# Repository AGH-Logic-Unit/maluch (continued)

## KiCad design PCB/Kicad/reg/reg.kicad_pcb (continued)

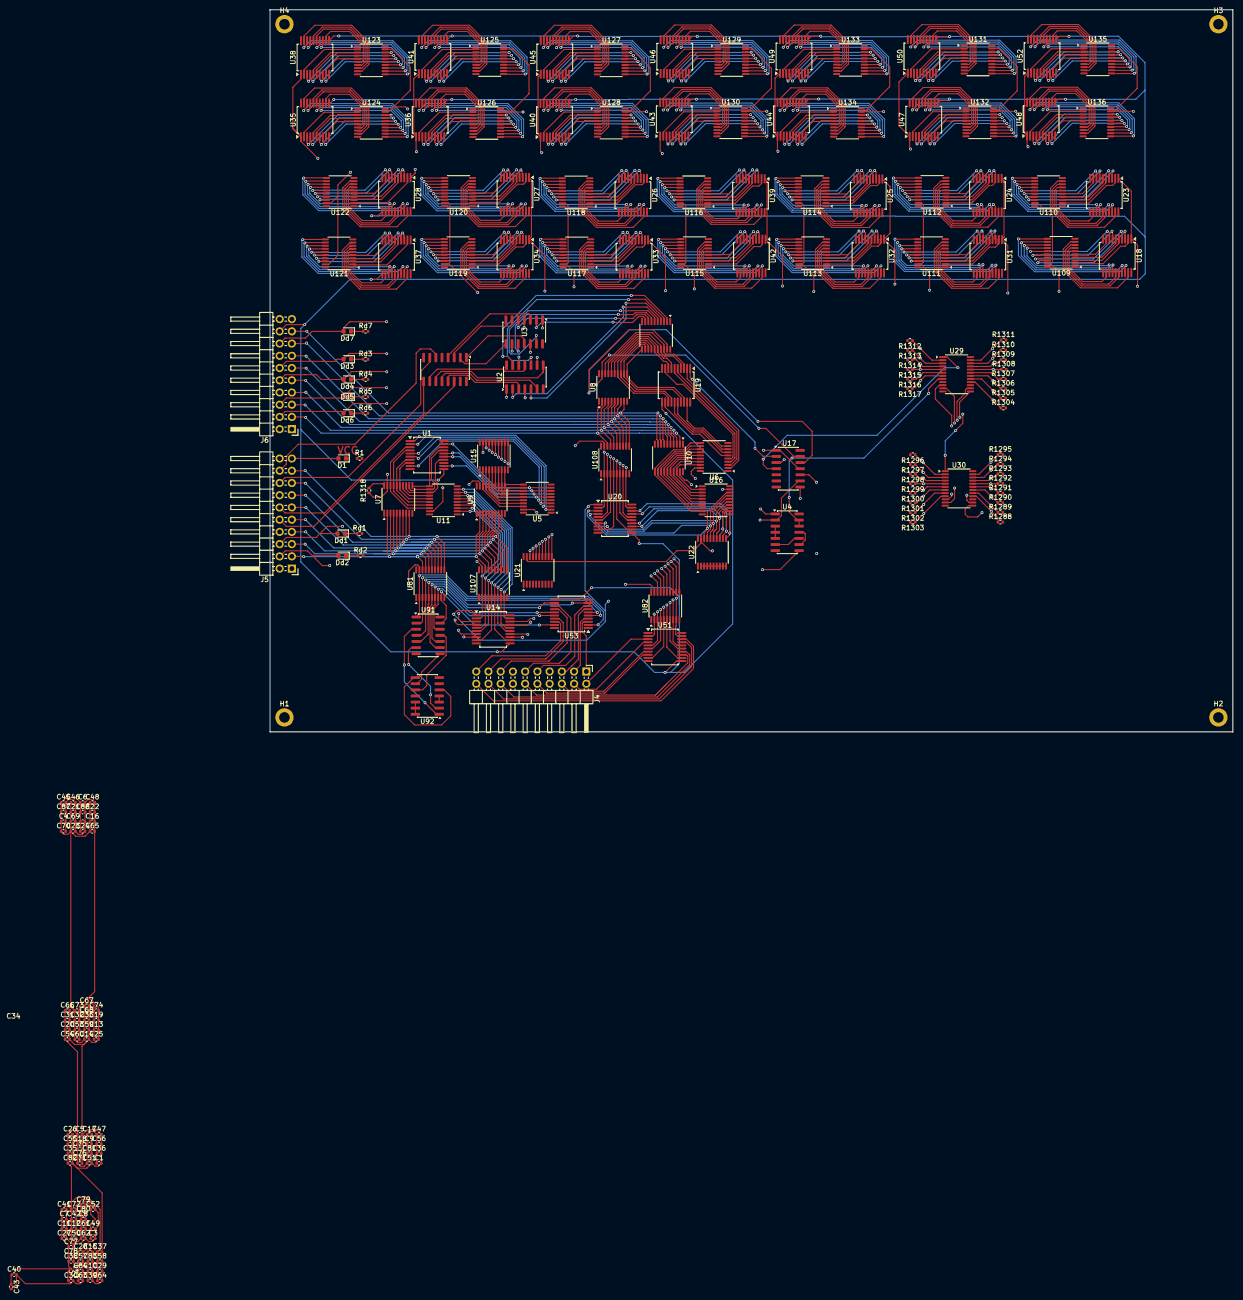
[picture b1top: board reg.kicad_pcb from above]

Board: 6 copper layers, 200.0 x 150.0 mm, 226 parts (0 on the bottom side), 428 nets.

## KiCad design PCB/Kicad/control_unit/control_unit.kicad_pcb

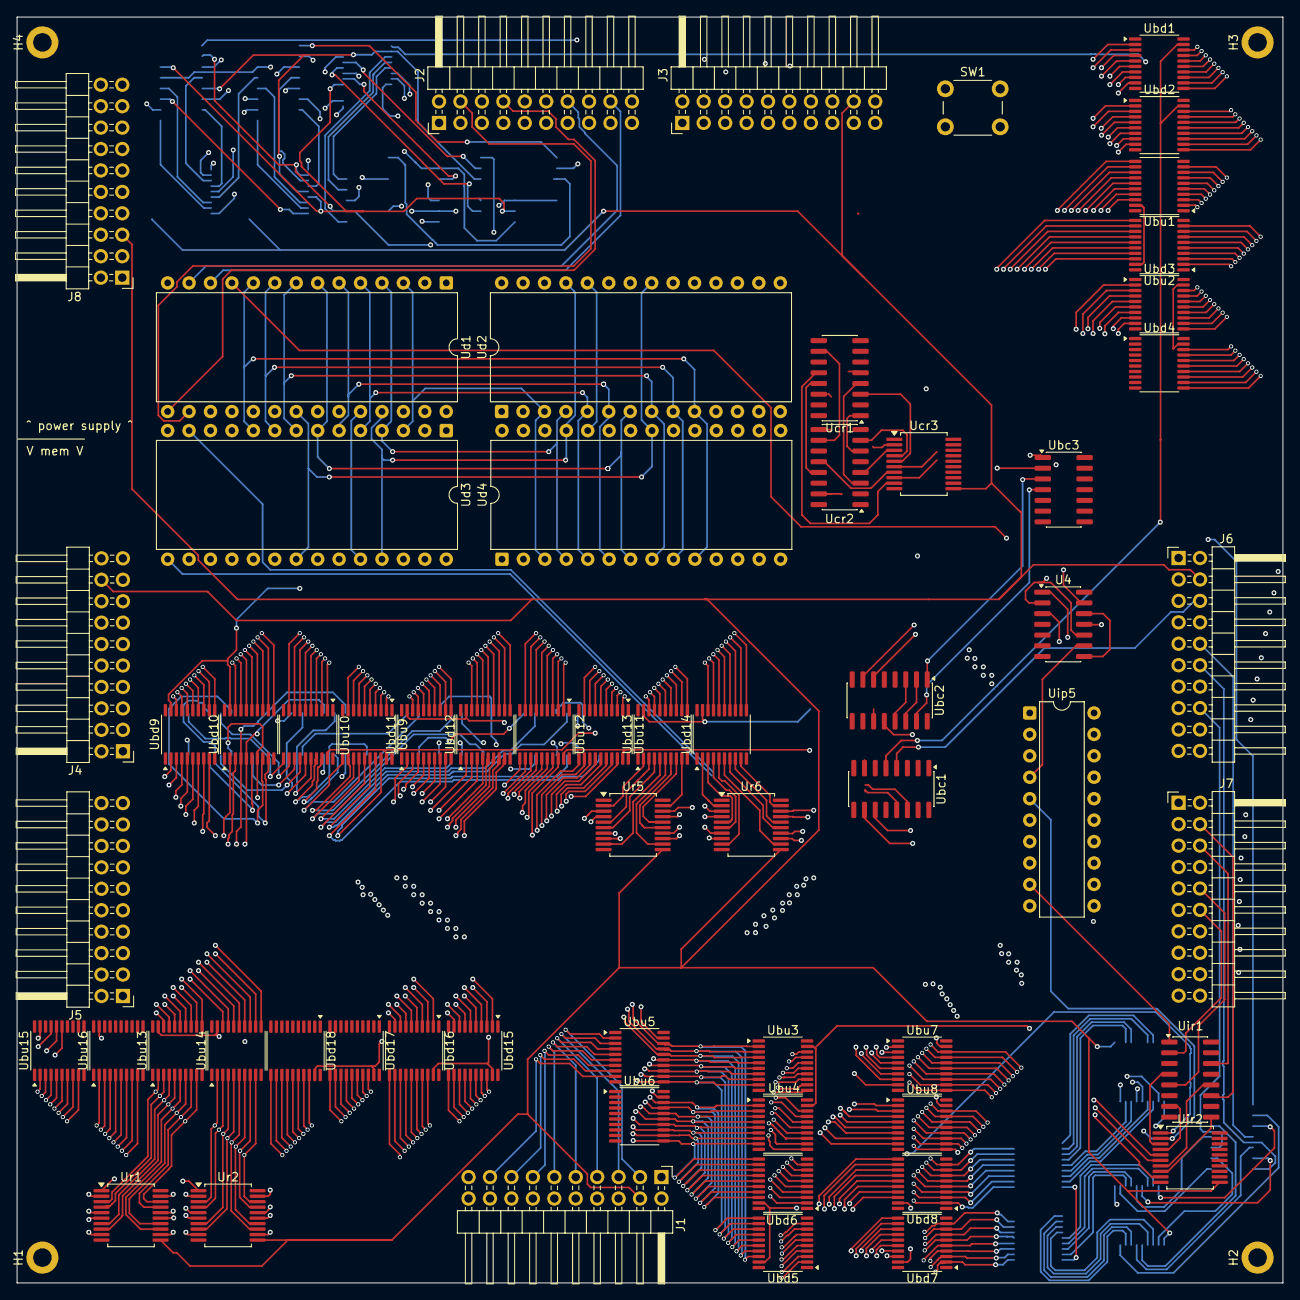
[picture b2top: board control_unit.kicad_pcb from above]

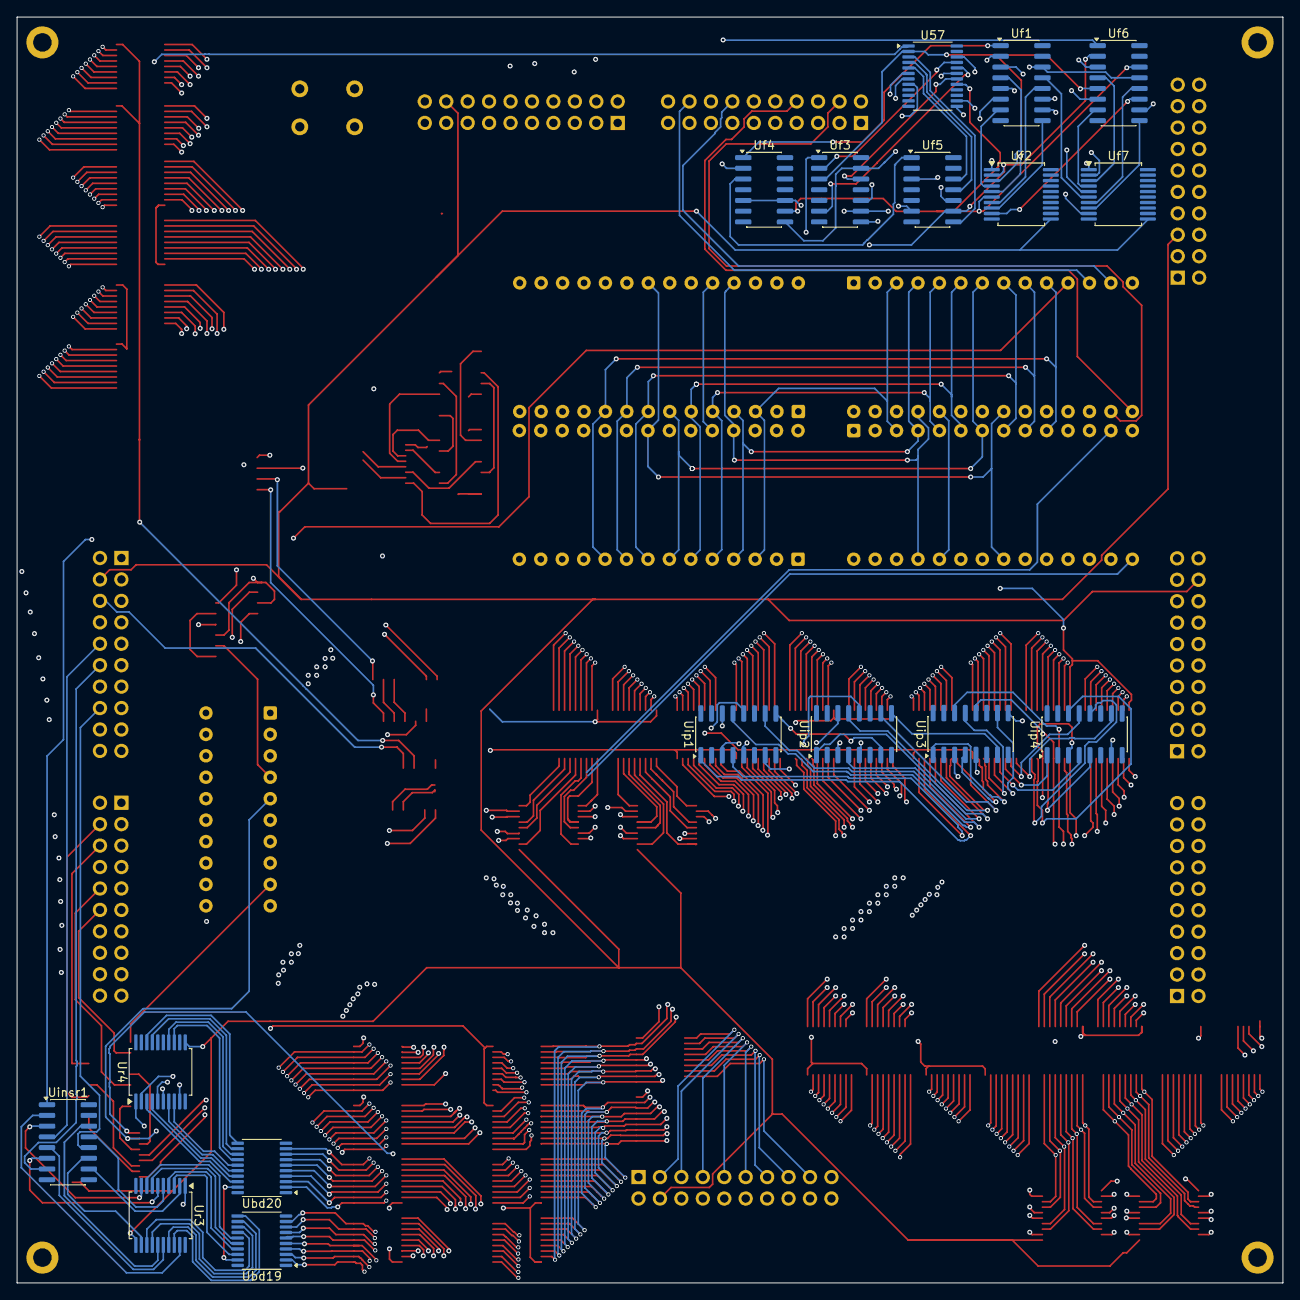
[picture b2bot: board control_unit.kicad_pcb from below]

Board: 6 copper layers, 150.0 x 150.0 mm, 82 parts (17 on the bottom side), 284 nets.

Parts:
H1, H2, H3, H4: MountingHole_Pad; MountingHole_2.2mm_M2_DIN965_Pad
J1, J2, J3, J4, J5, J6, J7, J8: in; PinHeader_2x10_P2.54mm_Horizontal
SW1: SW_Push; SW_PUSH_6mm_H4.3mm
U4: 7408; SO-14_3.9x8.65mm_P1.27mm
U57: 744067; TSSOP-24_4.4x7.8mm_P0.65mm
Ubc1, Ubc2: 74139; SOIC-16_3.9x9.9mm_P1.27mm
Ubc3: 7404; SO-14_3.9x8.65mm_P1.27mm
Ubd1, Ubd2, Ubd3, Ubd4, Ubd5, Ubd6, Ubd7, Ubd8, Ubd9, Ubd10, Ubd11, Ubd12, Ubd13, Ubd14, Ubd15, Ubd16, Ubd17, Ubd18, Ubd19, Ubd20: 74245; TSSOP-20_4.4x6.5mm_P0.65mm
Ubu1, Ubu2, Ubu3, Ubu4, Ubu5, Ubu6, Ubu7, Ubu8, Ubu9, Ubu10, Ubu11, Ubu12, Ubu13, Ubu14, Ubu15, Ubu16: 74245; TSSOP-20_4.4x6.5mm_P0.65mm
Ucr1: 74283; SOIC-16_3.9x9.9mm_P1.27mm
Ucr2: 74257; SOIC-16_3.9x9.9mm_P1.27mm
Ucr3: 74377; SSOP-20_5.3x7.2mm_P0.65mm
Ud1, Ud2, Ud3, Ud4: KM28C64A; DIP-28_W15.24mm
Uf1, Uf6: 74257; SOIC-16_3.9x9.9mm_P1.27mm
Uf2, Uf7: 74377; SSOP-20_5.3x7.2mm_P0.65mm
Uf3: 7404; SO-14_3.9x8.65mm_P1.27mm
Uf4: 7432; SO-14_3.9x8.65mm_P1.27mm
Uf5: 7486; SO-14_3.9x8.65mm_P1.27mm
Uinsr1: 74257; SOIC-16_3.9x9.9mm_P1.27mm
Uip1, Uip2, Uip3, Uip4: 74283; SOIC-16_3.9x9.9mm_P1.27mm
Uip5: ATF16V8Bxx-xxPU; DIP-20_W7.62mm
Uir1: 74257; SOIC-16_3.9x9.9mm_P1.27mm
Uir2: 74377; SSOP-20_5.3x7.2mm_P0.65mm
Ur1, Ur2, Ur3, Ur4, Ur5, Ur6: 74377; SSOP-20_5.3x7.2mm_P0.65mm

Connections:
/ControlUnit/alusrc0: Ubc1.14 (A0), Ud3.13 (I/O2)
/ControlUnit/alusrc1: Ubc1.13 (A1), Ud3.15 (I/O3)
/ControlUnit/buscntrl/srcbus0: Ubd5.18 (B0), Ubu3.2 (A0), Ubu5.18 (B0), Ubu11.18 (B0)
/ControlUnit/buscntrl/srcbus1: Ubd5.17 (B1), Ubu3.3 (A1), Ubu5.17 (B1), Ubu11.17 (B1)
/ControlUnit/buscntrl/srcbus2: Ubd5.16 (B2), Ubu3.4 (A2), Ubu5.16 (B2), Ubu11.16 (B2)
/ControlUnit/buscntrl/srcbus3: Ubd5.15 (B3), Ubu3.5 (A3), Ubu5.15 (B3), Ubu11.15 (B3)
/ControlUnit/buscntrl/srcbus4: Ubd5.14 (B4), Ubu3.6 (A4), Ubu5.14 (B4), Ubu11.14 (B4)
/ControlUnit/buscntrl/srcbus5: Ubd5.13 (B5), Ubu3.7 (A5), Ubu5.13 (B5), Ubu11.13 (B5)
/ControlUnit/buscntrl/srcbus6: Ubd5.12 (B6), Ubu3.8 (A6), Ubu5.12 (B6), Ubu11.12 (B6)
/ControlUnit/buscntrl/srcbus7: Ubd5.11 (B7), Ubu3.9 (A7), Ubu5.11 (B7), Ubu11.11 (B7)
/ControlUnit/buscntrl/srcbus8: Ubd6.18 (B0), Ubu4.2 (A0), Ubu6.18 (B0), Ubu12.18 (B0)
/ControlUnit/buscntrl/srcbus9: Ubd6.17 (B1), Ubu4.3 (A1), Ubu6.17 (B1), Ubu12.17 (B1)
/ControlUnit/buscntrl/srcbus10: Ubd6.16 (B2), Ubu4.4 (A2), Ubu6.16 (B2), Ubu12.16 (B2)
/ControlUnit/buscntrl/srcbus11: Ubd6.15 (B3), Ubu4.5 (A3), Ubu6.15 (B3), Ubu12.15 (B3)
/ControlUnit/buscntrl/srcbus12: Ubd6.14 (B4), Ubu4.6 (A4), Ubu6.14 (B4), Ubu12.14 (B4)
/ControlUnit/buscntrl/srcbus13: Ubd6.13 (B5), Ubu4.7 (A5), Ubu6.13 (B5), Ubu12.13 (B5)
/ControlUnit/buscntrl/srcbus14: Ubd6.12 (B6), Ubu4.8 (A6), Ubu6.12 (B6), Ubu12.12 (B6)
/ControlUnit/buscntrl/srcbus15: Ubd6.11 (B7), Ubu4.9 (A7), Ubu6.11 (B7), Ubu12.11 (B7)
/ControlUnit/buscntrl/~alu_membusen: Ubc1.11 (O1), Ubd7.19 (CE), Ubd8.19 (CE)
/ControlUnit/buscntrl/~alu_regbusen: Ubc1.10 (O2), Ubu7.19 (CE), Ubu8.19 (CE)
/ControlUnit/buscntrl/~mem_ipen: Ubc2.5 (O1), Ubd9.19 (CE), Ubd10.19 (CE)
/ControlUnit/buscntrl/~mem_ipnexten: Ubc2.6 (O2), Ubu9.19 (CE), Ubu10.19 (CE)
/ControlUnit/buscntrl/~mem_regbusen: Ubc2.7 (O3), Ubd11.19 (CE), Ubd12.19 (CE)
/ControlUnit/buscntrl/~mem_srcbusen: Ubc2.12 (O0), Ubu11.19 (CE), Ubu12.19 (CE)
/ControlUnit/buscntrl/~mem_tempregen: Ubc2.11 (O1), Ubd13.19 (CE), Ubd14.19 (CE)
/ControlUnit/buscntrl/~memsrc2: Ubc2.15 (E), Ubc3.4
/ControlUnit/buscntrl/~reg_alubusen: Ubc1.6 (O2), Ubu1.19 (CE), Ubu2.19 (CE)
/ControlUnit/buscntrl/~reg_iobusen: Ubc1.7 (O3), Ubd3.19 (CE), Ubd4.19 (CE)
/ControlUnit/buscntrl/~reg_membusen: Ubc1.5 (O1), Ubd1.19 (CE), Ubd2.19 (CE)
/ControlUnit/buscntrl/~src_regbusen: Ubc3.2, Ubu3.19 (CE), Ubu4.19 (CE)
/ControlUnit/cycle0: Ucr1.5 (A1), Ucr3.2 (Q0), Ud1.7 (A3), Ud2.7 (A3), Ud3.7 (A3), Ud4.7 (A3)
/ControlUnit/cycle1: Ucr1.3 (A2), Ucr3.5 (Q1), Ud1.6 (A4), Ud2.6 (A4), Ud3.6 (A4), Ud4.6 (A4)
/ControlUnit/cycle2: Ucr1.14 (A3), Ucr3.6 (Q2), Ud1.5 (A5), Ud2.5 (A5), Ud3.5 (A5), Ud4.5 (A5)
/ControlUnit/cycle3: Ucr1.12 (A4), Ucr3.9 (Q3), Ud1.4 (A6), Ud2.4 (A6), Ud3.4 (A6), Ud4.4 (A6)
/ControlUnit/flags/c: U57.17 (I14), Uf2.6 (Q2), Uf3.5, Uf4.9, Uf6.14 (I0c)
/ControlUnit/flags/nc: U57.20 (I11), Uf3.6
/ControlUnit/flags/no: U57.16 (I15), Uf3.4
/ControlUnit/flags/ns: U57.21 (I10), Uf3.2
/ControlUnit/flags/nz: U57.7 (I2), Uf3.8
/ControlUnit/flags/o: U57.2 (I7), Uf2.5 (Q1), Uf3.3, Uf5.10, Uf6.5 (I0b)
/ControlUnit/flags/s: U57.22 (I9), Uf2.2 (Q0), Uf3.1, Uf5.9, Uf6.2 (I0a)
/ControlUnit/flags/savedc: Uf1.13 (I1c), Uf7.6 (Q2)
/ControlUnit/flags/savedo: Uf1.6 (I1b), Uf7.5 (Q1)
/ControlUnit/flags/saveds: Uf1.3 (I1a), Uf7.2 (Q0)
/ControlUnit/flags/savedz: Uf1.10 (I1d), Uf7.9 (Q3)
/ControlUnit/flags/z: U57.8 (I1), Uf2.9 (Q3), Uf3.9, Uf4.5, Uf4.10, Uf6.11 (I0d)
/ControlUnit/flwe: Ud2.18 (I/O6), Uf4.2, Uf6.1 (S)
/ControlUnit/instructionregister/buffer_down/out0: Ubd19.18 (B0), Ur3.3 (D0)
/ControlUnit/instructionregister/buffer_down/out1: Ubd19.17 (B1), Ur3.4 (D1)
/ControlUnit/instructionregister/buffer_down/out2: Ubd19.16 (B2), Ur3.7 (D2)
/ControlUnit/instructionregister/buffer_down/out3: Ubd19.15 (B3), Ur3.8 (D3)
/ControlUnit/instructionregister/buffer_down/out4: Ubd19.14 (B4), Ur3.13 (D4)
/ControlUnit/instructionregister/buffer_down/out5: Ubd19.13 (B5), Ur3.14 (D5)
/ControlUnit/instructionregister/buffer_down/out6: Ubd19.12 (B6), Ur3.17 (D6)
/ControlUnit/instructionregister/buffer_down/out7: Ubd19.11 (B7), Ur3.18 (D7)
/ControlUnit/instructionregister/buffer_down/out8: Ubd20.18 (B0), Ur4.3 (D0)
/ControlUnit/instructionregister/buffer_down/out9: Ubd20.17 (B1), Ur4.4 (D1)
/ControlUnit/instructionregister/buffer_down/out10: Ubd20.16 (B2), Ur4.7 (D2)
/ControlUnit/instructionregister/buffer_down/out11: Ubd20.15 (B3), Ur4.8 (D3)
/ControlUnit/instructionregister/buffer_down/out12: Ubd20.14 (B4), Ur4.13 (D4)
/ControlUnit/instructionregister/buffer_down/out13: Ubd20.13 (B5), Ur4.14 (D5)
/ControlUnit/instructionregister/buffer_down/out14: Ubd20.12 (B6), Ur4.17 (D6)
/ControlUnit/instructionregister/buffer_down/out15: Ubd20.11 (B7), Ur4.18 (D7)
/ControlUnit/instructionregister/instr0: Uinsr1.10 (I1d), Ur3.2 (Q0)
/ControlUnit/instructionregister/instr1: Uinsr1.13 (I1c), Ur3.5 (Q1)
/ControlUnit/instructionregister/instr2: Uinsr1.6 (I1b), Ur3.6 (Q2)
/ControlUnit/instructionregister/instr3: Uinsr1.3 (I1a), Ur3.9 (Q3)
/ControlUnit/instructionregister/instr4: Uinsr1.11 (I0d), Ur3.12 (Q4)
/ControlUnit/instructionregister/instr5: Uinsr1.14 (I0c), Ur3.15 (Q5)
/ControlUnit/instructionregister/instr6: Uinsr1.5 (I0b), Ur3.16 (Q6)
/ControlUnit/instructionregister/instr7: Uinsr1.2 (I0a), Ur3.19 (Q7)
/ControlUnit/instructionregister/instr11: Uip1.7 (C0), Ur4.9 (Q3)
/ControlUnit/intidsaved0: Ubu15.17 (B1), Uir2.5 (Q1)
/ControlUnit/intidsaved1: Ubu15.16 (B2), Uir2.6 (Q2)
/ControlUnit/intidsaved2: Ubu15.15 (B3), Uir2.9 (Q3)
/ControlUnit/iosrc: Ubu5.19 (CE), Ubu6.19 (CE), Ud3.16 (I/O4)
/ControlUnit/ip0: Ubd9.2 (A0), Uip1.5 (A1), Ur1.2 (Q0)
/ControlUnit/ip1: Ubd9.3 (A1), Uip1.3 (A2), Ur1.5 (Q1)
/ControlUnit/ip2: Ubd9.4 (A2), Uip1.14 (A3), Ur1.6 (Q2)
/ControlUnit/ip3: Ubd9.5 (A3), Uip1.12 (A4), Ur1.9 (Q3)
/ControlUnit/ip4: Ubd9.6 (A4), Uip2.5 (A1), Ur1.12 (Q4)
/ControlUnit/ip5: Ubd9.7 (A5), Uip2.3 (A2), Ur1.15 (Q5)
/ControlUnit/ip6: Ubd9.8 (A6), Uip2.14 (A3), Ur1.16 (Q6)
/ControlUnit/ip7: Ubd9.9 (A7), Uip2.12 (A4), Ur1.19 (Q7)
/ControlUnit/ip8: Ubd10.2 (A0), Uip3.5 (A1), Ur2.2 (Q0)
/ControlUnit/ip9: Ubd10.3 (A1), Uip3.3 (A2), Ur2.5 (Q1)
/ControlUnit/ip10: Ubd10.4 (A2), Uip3.14 (A3), Ur2.6 (Q2)
/ControlUnit/ip11: Ubd10.5 (A3), Uip3.12 (A4), Ur2.9 (Q3)
/ControlUnit/ip12: Ubd10.6 (A4), Uip4.5 (A1), Ur2.12 (Q4)
/ControlUnit/ip13: Ubd10.7 (A5), Uip4.3 (A2), Ur2.15 (Q5)
/ControlUnit/ip14: Ubd10.8 (A6), Uip4.14 (A3), Ur2.16 (Q6)
/ControlUnit/ip15: Ubd10.9 (A7), Uip4.12 (A4), Ur2.19 (Q7)
/ControlUnit/ip/ipnew0: Ubd15.18 (B0), Ubd17.18 (B0), Ubu13.2 (A0), Ubu15.2 (A0), Ur1.3 (D0)
/ControlUnit/ip/ipnew1: Ubd15.17 (B1), Ubd17.17 (B1), Ubu13.3 (A1), Ubu15.3 (A1), Ur1.4 (D1)
/ControlUnit/ip/ipnew2: Ubd15.16 (B2), Ubd17.16 (B2), Ubu13.4 (A2), Ubu15.4 (A2), Ur1.7 (D2)
/ControlUnit/ip/ipnew3: Ubd15.15 (B3), Ubd17.15 (B3), Ubu13.5 (A3), Ubu15.5 (A3), Ur1.8 (D3)
/ControlUnit/ip/ipnew4: Ubd15.14 (B4), Ubd17.14 (B4), Ubu13.6 (A4), Ubu15.6 (A4), Ur1.13 (D4)
/ControlUnit/ip/ipnew5: Ubd15.13 (B5), Ubd17.13 (B5), Ubu13.7 (A5), Ubu15.7 (A5), Ur1.14 (D5)
/ControlUnit/ip/ipnew6: Ubd15.12 (B6), Ubd17.12 (B6), Ubu13.8 (A6), Ubu15.8 (A6), Ur1.17 (D6)
/ControlUnit/ip/ipnew7: Ubd15.11 (B7), Ubd17.11 (B7), Ubu13.9 (A7), Ubu15.9 (A7), Ur1.18 (D7)
/ControlUnit/ip/ipnew8: Ubd16.18 (B0), Ubd18.18 (B0), Ubu14.2 (A0), Ubu16.2 (A0), Ur2.3 (D0)
/ControlUnit/ip/ipnew9: Ubd16.17 (B1), Ubd18.17 (B1), Ubu14.3 (A1), Ubu16.3 (A1), Ur2.4 (D1)
/ControlUnit/ip/ipnew10: Ubd16.16 (B2), Ubd18.16 (B2), Ubu14.4 (A2), Ubu16.4 (A2), Ur2.7 (D2)
/ControlUnit/ip/ipnew11: Ubd16.15 (B3), Ubd18.15 (B3), Ubu14.5 (A3), Ubu16.5 (A3), Ur2.8 (D3)
/ControlUnit/ip/ipnew12: Ubd16.14 (B4), Ubd18.14 (B4), Ubu14.6 (A4), Ubu16.6 (A4), Ur2.13 (D4)
/ControlUnit/ip/ipnew13: Ubd16.13 (B5), Ubd18.13 (B5), Ubu14.7 (A5), Ubu16.7 (A5), Ur2.14 (D5)
/ControlUnit/ip/ipnew14: Ubd16.12 (B6), Ubd18.12 (B6), Ubu14.8 (A6), Ubu16.8 (A6), Ur2.17 (D6)
/ControlUnit/ip/ipnew15: Ubd16.11 (B7), Ubd18.11 (B7), Ubu14.9 (A7), Ubu16.9 (A7), Ur2.18 (D7)
/ControlUnit/ip/~intidbusen: Ubu15.19 (CE), Ubu16.19 (CE), Uip5.15 (I/O)
/ControlUnit/ip/~ipincen: Ubd15.19 (CE), Ubd16.19 (CE), Uip5.12 (I/O)
/ControlUnit/ip/~membusen: Ubu13.19 (CE), Ubu14.19 (CE), Uip5.14 (I/O)
/ControlUnit/ip/~srcbusen: Ubd17.19 (CE), Ubd18.19 (CE), Uip5.13 (I/O)
/ControlUnit/ipnext0: Ubd15.2 (A0), Ubu9.18 (B0), Uip1.4 (S1)
/ControlUnit/ipnext1: Ubd15.3 (A1), Ubu9.17 (B1), Uip1.1 (S2)
/ControlUnit/ipnext2: Ubd15.4 (A2), Ubu9.16 (B2), Uip1.13 (S3)
/ControlUnit/ipnext3: Ubd15.5 (A3), Ubu9.15 (B3), Uip1.10 (S4)
/ControlUnit/ipnext4: Ubd15.6 (A4), Ubu9.14 (B4), Uip2.4 (S1)
/ControlUnit/ipnext5: Ubd15.7 (A5), Ubu9.13 (B5), Uip2.1 (S2)
/ControlUnit/ipnext6: Ubd15.8 (A6), Ubu9.12 (B6), Uip2.13 (S3)
/ControlUnit/ipnext7: Ubd15.9 (A7), Ubu9.11 (B7), Uip2.10 (S4)
/ControlUnit/ipnext8: Ubd16.2 (A0), Ubu10.18 (B0), Uip3.4 (S1)
/ControlUnit/ipnext9: Ubd16.3 (A1), Ubu10.17 (B1), Uip3.1 (S2)
/ControlUnit/ipnext10: Ubd16.4 (A2), Ubu10.16 (B2), Uip3.13 (S3)
/ControlUnit/ipnext11: Ubd16.5 (A3), Ubu10.15 (B3), Uip3.10 (S4)
/ControlUnit/ipnext12: Ubd16.6 (A4), Ubu10.14 (B4), Uip4.4 (S1)
/ControlUnit/ipnext13: Ubd16.7 (A5), Ubu10.13 (B5), Uip4.1 (S2)
/ControlUnit/ipnext14: Ubd16.8 (A6), Ubu10.12 (B6), Uip4.13 (S3)
/ControlUnit/ipnext15: Ubd16.9 (A7), Ubu10.11 (B7), Uip4.10 (S4)
/ControlUnit/isint: Ubd19.19 (CE), Ubd20.19 (CE), Uip5.5 (I4), Uir2.2 (Q0)
/ControlUnit/isjump: Ud2.16 (I/O4), Uip5.2 (I1)
/ControlUnit/isret: U4.9, Ud1.19 (I/O7), Uip5.4 (I3)
/ControlUnit/isstack: Ud4.11 (I/O0), Uinsr1.15 (OE)
/ControlUnit/memsrc0: Ubc2.2 (A0), Ubc2.14 (A0), Ud3.17 (I/O5)
/ControlUnit/memsrc1: Ubc2.3 (A1), Ubc2.13 (A1), Ud3.18 (I/O6)
/ControlUnit/memsrc2: Ubc2.1 (E), Ubc3.3, Ud3.19 (I/O7)
/ControlUnit/next_instr: U4.2, U4.10, Ubc3.11, Ud1.11 (I/O0)
/ControlUnit/opcode0: U57.13 (S3), Ud1.3 (A7), Ud2.3 (A7), Ud3.3 (A7), Ud4.3 (A7), Ur4.12 (Q4)
/ControlUnit/opcode1: Ud1.25 (A8), Ud2.25 (A8), Ud3.25 (A8), Ud4.25 (A8), Ur4.15 (Q5)
/ControlUnit/opcode2: Ud1.24 (A9), Ud2.24 (A9), Ud3.24 (A9), Ud4.24 (A9), Ur4.16 (Q6)
/ControlUnit/opcode3: Ud1.21 (A10), Ud2.21 (A10), Ud3.21 (A10), Ud4.21 (A10), Ur4.19 (Q7)
/ControlUnit/regds: Ud4.12 (I/O1), Uinsr1.1 (S)
/ControlUnit/regsrc0: Ubc1.2 (A0), Ud3.11 (I/O0)
/ControlUnit/regsrc1: Ubc1.3 (A1), Ud3.12 (I/O1)
/ControlUnit/rst: SW1.2, Ucr2.15 (OE), Uip5.9 (I8), Uir1.1 (S)
/ControlUnit/should_jump: U57.1 (COM_I/O), Uip5.3 (I2)
/ControlUnit/srcsrc: Ubc3.1, Ubd5.19 (CE), Ubd6.19 (CE), Ud2.19 (I/O7)
/ControlUnit/tempreg0: Ubd13.2 (A0), Ur5.2 (Q0)
/ControlUnit/tempreg1: Ubd13.3 (A1), Ur5.5 (Q1)
/ControlUnit/tempreg2: Ubd13.4 (A2), Ur5.6 (Q2)
/ControlUnit/tempreg3: Ubd13.5 (A3), Ur5.9 (Q3)
/ControlUnit/tempreg4: Ubd13.6 (A4), Ur5.12 (Q4)
/ControlUnit/tempreg5: Ubd13.7 (A5), Ur5.15 (Q5)
/ControlUnit/tempreg6: Ubd13.8 (A6), Ur5.16 (Q6)
/ControlUnit/tempreg7: Ubd13.9 (A7), Ur5.19 (Q7)
/ControlUnit/tempreg8: Ubd14.2 (A0), Ur6.2 (Q0)
/ControlUnit/tempreg9: Ubd14.3 (A1), Ur6.5 (Q1)
/ControlUnit/tempreg10: Ubd14.4 (A2), Ur6.6 (Q2)
/ControlUnit/tempreg11: Ubd14.5 (A3), Ur6.9 (Q3)
/ControlUnit/tempreg12: Ubd14.6 (A4), Ur6.12 (Q4)
/ControlUnit/tempreg13: Ubd14.7 (A5), Ur6.15 (Q5)
/ControlUnit/tempreg14: Ubd14.8 (A6), Ur6.16 (Q6)
/ControlUnit/tempreg15: Ubd14.9 (A7), Ur6.19 (Q7)
/ControlUnit/~instr_load: Ud2.11 (I/O0), Ur3.1 (~E), Ur4.1 (~E)
/ControlUnit/~next_instr: Ubc3.10, Ucr2.1 (S), Uir2.1 (~E), Ur1.1 (~E), Ur2.1 (~E)
/ControlUnit/~tempregwe: Ud2.17 (I/O5), Ur5.1 (~E), Ur6.1 (~E)
/alubus0: J3.17, Ubd7.18 (B0), Ubu1.18 (B0), Ubu7.2 (A0)
/alubus1: J3.15, Ubd7.17 (B1), Ubu1.17 (B1), Ubu7.3 (A1)
/alubus2: J3.13, Ubd7.16 (B2), Ubu1.16 (B2), Ubu7.4 (A2)
/alubus3: J3.11, Ubd7.15 (B3), Ubu1.15 (B3), Ubu7.5 (A3)
/alubus4: J3.9, Ubd7.14 (B4), Ubu1.14 (B4), Ubu7.6 (A4)
/alubus5: J3.7, Ubd7.13 (B5), Ubu1.13 (B5), Ubu7.7 (A5)
/alubus6: J3.5, Ubd7.12 (B6), Ubu1.12 (B6), Ubu7.8 (A6)
/alubus7: J3.3, Ubd7.11 (B7), Ubu1.11 (B7), Ubu7.9 (A7)
/alubus8: J2.17, Ubd8.18 (B0), Ubu2.18 (B0), Ubu8.2 (A0)
/alubus9: J2.15, Ubd8.17 (B1), Ubu2.17 (B1), Ubu8.3 (A1)
/alubus10: J2.13, Ubd8.16 (B2), Ubu2.16 (B2), Ubu8.4 (A2)
/alubus11: J2.11, Ubd8.15 (B3), Ubu2.15 (B3), Ubu8.5 (A3)
/alubus12: J2.9, Ubd8.14 (B4), Ubu2.14 (B4), Ubu8.6 (A4)
/alubus13: J2.7, Ubd8.13 (B5), Ubu2.13 (B5), Ubu8.7 (A5)
/alubus14: J2.5, Ubd8.12 (B6), Ubu2.12 (B6), Ubu8.8 (A6)
/alubus15: J2.3, Ubd8.11 (B7), Ubu2.11 (B7), Ubu8.9 (A7)
/aluop0: J2.18, Ud1.12 (I/O1)
/aluop1: J2.14, Ud1.13 (I/O2)
/aluop2: J2.8, Ud1.15 (I/O3)
/aluop3: J2.4, Ud1.16 (I/O4)
/clk: J1.4, J3.18, J4.18, J6.4, J8.3, J8.5, Ucr3.11 (CP), Uf2.11 (CP), Uf7.11 (CP), Uir2.11 (CP), Ur1.11 (CP), Ur2.11 (CP), Ur3.11 (CP), Ur4.11 (CP), Ur5.11 (CP), Ur6.11 (CP)
/fc: J3.10, Uf1.14 (I0c), Uf6.13 (I1c)
/fo: J3.6, Uf1.5 (I0b), Uf6.6 (I1b)
/fs: J3.4, Uf1.2 (I0a), Uf6.3 (I1a)
/fz: J3.12, Uf1.11 (I0d), Uf6.10 (I1d)
/int: J7.12, U4.1, Uir1.2 (I0a)
/intid0: J7.10, Uir1.5 (I0b)
/intid1: J7.6, Uir1.14 (I0c)
/intid2: J7.4, Uir1.11 (I0d)
/iobus0: J1.3, Ubd3.2 (A0), Ubu5.2 (A0)
/iobus1: J1.5, Ubd3.3 (A1), Ubu5.3 (A1)
/iobus2: J1.7, Ubd3.4 (A2), Ubu5.4 (A2)
/iobus3: J1.9, Ubd3.5 (A3), Ubu5.5 (A3)
/iobus4: J1.11, Ubd3.6 (A4), Ubu5.6 (A4)
/iobus5: J1.13, Ubd3.7 (A5), Ubu5.7 (A5)
/iobus6: J1.15, Ubd3.8 (A6), Ubu5.8 (A6)
/iobus7: J1.17, Ubd3.9 (A7), Ubu5.9 (A7)
/iocmd0: J1.16, Ud1.17 (I/O5)
/iocmd1: J1.18, Ud1.18 (I/O6)
/ioid0: J1.6, U4.13, U57.10 (S0), Ud1.10 (A0), Ud2.10 (A0), Ud3.10 (A0), Ud4.10 (A0), Ur4.2 (Q0)
/ioid1: J1.10, U57.11 (S1), Ud1.9 (A1), Ud2.9 (A1), Ud3.9 (A1), Ud4.9 (A1), Ur4.5 (Q1)
/ioid2: J1.12, U57.14 (S2), Ud1.8 (A2), Ud2.8 (A2), Ud3.8 (A2), Ud4.8 (A2), Ur4.6 (Q2)
/mask_restore: J7.18, U4.11, Uf1.1 (S), Uf4.1
/mask_save: J7.16, U4.3, Uf5.4
/membus0: J5.3, Ubd1.2 (A0), Ubd5.2 (A0), Ubd7.2 (A0), Ubd9.18 (B0), Ubd11.18 (B0), Ubd13.18 (B0), Ubd19.2 (A0), Ubu9.2 (A0), Ubu11.2 (A0), Ubu13.18 (B0), Ur5.3 (D0)
/membus1: J5.5, Ubd1.3 (A1), Ubd5.3 (A1), Ubd7.3 (A1), Ubd9.17 (B1), Ubd11.17 (B1), Ubd13.17 (B1), Ubd19.3 (A1), Ubu9.3 (A1), Ubu11.3 (A1), Ubu13.17 (B1), Ur5.4 (D1)
/membus2: J5.7, Ubd1.4 (A2), Ubd5.4 (A2), Ubd7.4 (A2), Ubd9.16 (B2), Ubd11.16 (B2), Ubd13.16 (B2), Ubd19.4 (A2), Ubu9.4 (A2), Ubu11.4 (A2), Ubu13.16 (B2), Ur5.7 (D2)
/membus3: J5.9, Ubd1.5 (A3), Ubd5.5 (A3), Ubd7.5 (A3), Ubd9.15 (B3), Ubd11.15 (B3), Ubd13.15 (B3), Ubd19.5 (A3), Ubu9.5 (A3), Ubu11.5 (A3), Ubu13.15 (B3), Ur5.8 (D3)
/membus4: J5.11, Ubd1.6 (A4), Ubd5.6 (A4), Ubd7.6 (A4), Ubd9.14 (B4), Ubd11.14 (B4), Ubd13.14 (B4), Ubd19.6 (A4), Ubu9.6 (A4), Ubu11.6 (A4), Ubu13.14 (B4), Ur5.13 (D4)
/membus5: J5.13, Ubd1.7 (A5), Ubd5.7 (A5), Ubd7.7 (A5), Ubd9.13 (B5), Ubd11.13 (B5), Ubd13.13 (B5), Ubd19.7 (A5), Ubu9.7 (A5), Ubu11.7 (A5), Ubu13.13 (B5), Ur5.14 (D5)
/membus6: J5.15, Ubd1.8 (A6), Ubd5.8 (A6), Ubd7.8 (A6), Ubd9.12 (B6), Ubd11.12 (B6), Ubd13.12 (B6), Ubd19.8 (A6), Ubu9.8 (A6), Ubu11.8 (A6), Ubu13.12 (B6), Ur5.17 (D6)
/membus7: J5.17, Ubd1.9 (A7), Ubd5.9 (A7), Ubd7.9 (A7), Ubd9.11 (B7), Ubd11.11 (B7), Ubd13.11 (B7), Ubd19.9 (A7), Ubu9.9 (A7), Ubu11.9 (A7), Ubu13.11 (B7), Ur5.18 (D7)
/membus8: J4.3, Ubd2.2 (A0), Ubd6.2 (A0), Ubd8.2 (A0), Ubd10.18 (B0), Ubd12.18 (B0), Ubd14.18 (B0), Ubd20.2 (A0), Ubu10.2 (A0), Ubu12.2 (A0), Ubu14.18 (B0), Ur6.3 (D0)
/membus9: J4.5, Ubd2.3 (A1), Ubd6.3 (A1), Ubd8.3 (A1), Ubd10.17 (B1), Ubd12.17 (B1), Ubd14.17 (B1), Ubd20.3 (A1), Ubu10.3 (A1), Ubu12.3 (A1), Ubu14.17 (B1), Ur6.4 (D1)
/membus10: J4.7, Ubd2.4 (A2), Ubd6.4 (A2), Ubd8.4 (A2), Ubd10.16 (B2), Ubd12.16 (B2), Ubd14.16 (B2), Ubd20.4 (A2), Ubu10.4 (A2), Ubu12.4 (A2), Ubu14.16 (B2), Ur6.7 (D2)
/membus11: J4.9, Ubd2.5 (A3), Ubd6.5 (A3), Ubd8.5 (A3), Ubd10.15 (B3), Ubd12.15 (B3), Ubd14.15 (B3), Ubd20.5 (A3), Ubu10.5 (A3), Ubu12.5 (A3), Ubu14.15 (B3), Ur6.8 (D3)
/membus12: J4.11, Ubd2.6 (A4), Ubd6.6 (A4), Ubd8.6 (A4), Ubd10.14 (B4), Ubd12.14 (B4), Ubd14.14 (B4), Ubd20.6 (A4), Ubu10.6 (A4), Ubu12.6 (A4), Ubu14.14 (B4), Ur6.13 (D4)
/membus13: J4.13, Ubd2.7 (A5), Ubd6.7 (A5), Ubd8.7 (A5), Ubd10.13 (B5), Ubd12.13 (B5), Ubd14.13 (B5), Ubd20.7 (A5), Ubu10.7 (A5), Ubu12.7 (A5), Ubu14.13 (B5), Ur6.14 (D5)
/membus14: J4.15, Ubd2.8 (A6), Ubd6.8 (A6), Ubd8.8 (A6), Ubd10.12 (B6), Ubd12.12 (B6), Ubd14.12 (B6), Ubd20.8 (A6), Ubu10.8 (A6), Ubu12.8 (A6), Ubu14.12 (B6), Ur6.17 (D6)
/membus15: J4.17, Ubd2.9 (A7), Ubd6.9 (A7), Ubd8.9 (A7), Ubd10.11 (B7), Ubd12.11 (B7), Ubd14.11 (B7), Ubd20.9 (A7), Ubu10.9 (A7), Ubu12.9 (A7), Ubu14.11 (B7), Ur6.18 (D7)
/memop0: J5.4, Ud2.12 (I/O1)
/memop1: J5.8, Ud2.13 (I/O2)
/memop2: J5.12, Ud2.15 (I/O3)
/regbus0: J7.17, Ubd1.18 (B0), Ubd3.18 (B0), Ubd11.2 (A0), Ubu1.2 (A0), Ubu3.18 (B0), Ubu7.18 (B0)
/regbus1: J7.15, Ubd1.17 (B1), Ubd3.17 (B1), Ubd11.3 (A1), Ubu1.3 (A1), Ubu3.17 (B1), Ubu7.17 (B1)
/regbus2: J7.13, Ubd1.16 (B2), Ubd3.16 (B2), Ubd11.4 (A2), Ubu1.4 (A2), Ubu3.16 (B2), Ubu7.16 (B2)
/regbus3: J7.11, Ubd1.15 (B3), Ubd3.15 (B3), Ubd11.5 (A3), Ubu1.5 (A3), Ubu3.15 (B3), Ubu7.15 (B3)
/regbus4: J7.9, Ubd1.14 (B4), Ubd3.14 (B4), Ubd11.6 (A4), Ubu1.6 (A4), Ubu3.14 (B4), Ubu7.14 (B4)
/regbus5: J7.7, Ubd1.13 (B5), Ubd3.13 (B5), Ubd11.7 (A5), Ubu1.7 (A5), Ubu3.13 (B5), Ubu7.13 (B5)
/regbus6: J7.5, Ubd1.12 (B6), Ubd3.12 (B6), Ubd11.8 (A6), Ubu1.8 (A6), Ubu3.12 (B6), Ubu7.12 (B6)
/regbus7: J7.3, Ubd1.11 (B7), Ubd3.11 (B7), Ubd11.9 (A7), Ubu1.9 (A7), Ubu3.11 (B7), Ubu7.11 (B7)
/regbus8: J6.17, Ubd2.18 (B0), Ubd4.18 (B0), Ubd12.2 (A0), Ubu2.2 (A0), Ubu4.18 (B0), Ubu8.18 (B0)
/regbus9: J6.15, Ubd2.17 (B1), Ubd4.17 (B1), Ubd12.3 (A1), Ubu2.3 (A1), Ubu4.17 (B1), Ubu8.17 (B1)
/regbus10: J6.13, Ubd2.16 (B2), Ubd4.16 (B2), Ubd12.4 (A2), Ubu2.4 (A2), Ubu4.16 (B2), Ubu8.16 (B2)
/regbus11: J6.11, Ubd2.15 (B3), Ubd4.15 (B3), Ubd12.5 (A3), Ubu2.5 (A3), Ubu4.15 (B3), Ubu8.15 (B3)
/regbus12: J6.9, Ubd2.14 (B4), Ubd4.14 (B4), Ubd12.6 (A4), Ubu2.6 (A4), Ubu4.14 (B4), Ubu8.14 (B4)
/regbus13: J6.7, Ubd2.13 (B5), Ubd4.13 (B5), Ubd12.7 (A5), Ubu2.7 (A5), Ubu4.13 (B5), Ubu8.13 (B5)
/regbus14: J6.5, Ubd2.12 (B6), Ubd4.12 (B6), Ubd12.8 (A6), Ubu2.8 (A6), Ubu4.12 (B6), Ubu8.12 (B6)
/regbus15: J6.3, Ubd2.11 (B7), Ubd4.11 (B7), Ubd12.9 (A7), Ubu2.9 (A7), Ubu4.11 (B7), Ubu8.11 (B7)
/regwe: J6.6, Ubc1.4 (O0)
/rid0: J6.18, Uinsr1.9 (Zd)
/rid1: J6.16, Uinsr1.12 (Zc)
/rid2: J6.12, Uinsr1.7 (Zb)
/rid3: J6.10, Uinsr1.4 (Za)
GND: H1.1 (1_1), H2.1 (1_1), H3.1 (1_1), H4.1 (1_1), J1.2, J1.8, J1.14, J1.20, J2.2, J2.6, J2.10, J2.12, J2.16, J2.20, J3.2, J3.8, J3.14, J3.16, J3.20, J4.2, J4.4, J4.6, J4.8, J4.10, J4.12, J4.14, J4.16, J4.20, J5.2, J5.6, J5.10, J5.14, J5.16, J5.18, J5.20, J6.2, J6.8, J6.14, J6.20, J7.2, J7.8, J7.14, J7.20, J8.1, J8.2, J8.4, J8.6, J8.7, J8.8, J8.10, J8.12, J8.14, J8.16, J8.18, J8.20, U4.7 (GND), U57.12 (GND), U57.15 (~E), U57.23 (I8), Ubc1.1 (E), Ubc1.8 (GND), Ubc1.15 (E), Ubc2.8 (GND), Ubc3.7 (GND), Ubd1.10 (GND), Ubd2.10 (GND), Ubd3.10 (GND), Ubd4.2 (A0), Ubd4.3 (A1), Ubd4.4 (A2), Ubd4.5 (A3), Ubd4.6 (A4), Ubd4.7 (A5), Ubd4.8 (A6), Ubd4.9 (A7), Ubd4.10 (GND), Ubd5.10 (GND), Ubd6.10 (GND), Ubd7.10 (GND), Ubd8.10 (GND), Ubd9.10 (GND), Ubd10.10 (GND), Ubd11.10 (GND), Ubd12.10 (GND), Ubd13.10 (GND), Ubd14.10 (GND), Ubd15.10 (GND), Ubd16.10 (GND), Ubd17.10 (GND), Ubd18.10 (GND), Ubd19.10 (GND), Ubd20.10 (GND), Ubu1.1 (A->B), Ubu1.10 (GND), Ubu2.1 (A->B), Ubu2.10 (GND), Ubu3.1 (A->B), Ubu3.10 (GND), Ubu4.1 (A->B), Ubu4.10 (GND), Ubu5.1 (A->B), Ubu5.10 (GND), Ubu6.1 (A->B), Ubu6.2 (A0), Ubu6.3 (A1), Ubu6.4 (A2), Ubu6.5 (A3), Ubu6.6 (A4), Ubu6.7 (A5), Ubu6.8 (A6), Ubu6.9 (A7), Ubu6.10 (GND), Ubu7.1 (A->B), Ubu7.10 (GND), Ubu8.1 (A->B), Ubu8.10 (GND), Ubu9.1 (A->B), Ubu9.10 (GND), Ubu10.1 (A->B), Ubu10.10 (GND), Ubu11.1 (A->B), Ubu11.10 (GND), Ubu12.1 (A->B), Ubu12.10 (GND), Ubu13.1 (A->B), Ubu13.10 (GND), Ubu14.1 (A->B), Ubu14.10 (GND), Ubu15.1 (A->B), Ubu15.10 (GND), Ubu15.18 (B0), Ubu16.1 (A->B), Ubu16.10 (GND), Ucr1.2 (B2), Ucr1.6 (B1), Ucr1.8 (GND), Ucr1.11 (B4), Ucr1.15 (B3), Ucr2.2 (I0a), Ucr2.5 (I0b), Ucr2.8 (GND), Ucr2.11 (I0d), Ucr2.14 (I0c), Ucr3.1 (~E), Ucr3.10 (GND), Ud1.2 (A12), Ud1.14 (GND), Ud1.20 (~CE), Ud1.22 (~OE), Ud1.23 (A11), Ud2.2 (A12), Ud2.14 (GND), Ud2.20 (~CE), Ud2.22 (~OE), Ud2.23 (A11), Ud3.2 (A12), Ud3.14 (GND), Ud3.20 (~CE), Ud3.22 (~OE), Ud3.23 (A11), Ud4.2 (A12), Ud4.14 (GND), Ud4.20 (~CE), Ud4.22 (~OE), Ud4.23 (A11), Uf1.8 (GND), Uf1.15 (OE), Uf2.10 (GND), Uf3.7 (GND), Uf4.7 (GND), Uf5.7 (GND), Uf6.8 (GND), Uf6.15 (OE), Uf7.10 (GND), Uinsr1.8 (GND), Uip1.2 (B2), Uip1.8 (GND), Uip1.11 (B4), Uip1.15 (B3), Uip2.2 (B2), Uip2.6 (B1), Uip2.8 (GND), Uip2.11 (B4), Uip2.15 (B3), Uip3.2 (B2), Uip3.6 (B1), Uip3.8 (GND), Uip3.11 (B4), Uip3.15 (B3), Uip4.2 (B2), Uip4.6 (B1), Uip4.8 (GND), Uip4.11 (B4), Uip4.15 (B3), Uip5.1 (I), Uip5.6 (I5), Uip5.7 (I6), Uip5.8 (I7), Uip5.10 (GND), Uip5.11 (I9), Uir1.3 (I1a), Uir1.6 (I1b), Uir1.8 (GND), Uir1.10 (I1d), Uir1.13 (I1c), Uir1.15 (OE), Uir2.10 (GND), Ur1.10 (GND), Ur2.10 (GND), Ur3.10 (GND), Ur4.10 (GND), Ur5.10 (GND), Ur6.10 (GND)
unnamed: U4.8, U4.12
unnamed: U57.6 (I3), Uf3.10
unnamed: U57.5 (I4), Uf4.6, Uf5.12
unnamed: U57.4 (I5), Uf5.11
unnamed: U57.3 (I6), Uf3.11, Uf4.4, Uf5.8
unnamed: U57.19 (I12), Uf3.13, Uf4.8
unnamed: U57.18 (I13), Uf3.12
unnamed: Ucr1.4 (S1), Ucr2.3 (I1a)
unnamed: Ucr1.1 (S2), Ucr2.6 (I1b)
unnamed: Ucr1.13 (S3), Ucr2.13 (I1c)
unnamed: Ucr1.10 (S4), Ucr2.10 (I1d)
unnamed: Ucr2.4 (Za), Ucr3.3 (D0)
unnamed: Ucr2.7 (Zb), Ucr3.4 (D1)
unnamed: Ucr2.12 (Zc), Ucr3.7 (D2)
unnamed: Ucr2.9 (Zd), Ucr3.8 (D3)
unnamed: Uf1.4 (Za), Uf2.3 (D0)
unnamed: Uf1.7 (Zb), Uf2.4 (D1)
unnamed: Uf1.12 (Zc), Uf2.7 (D2)
unnamed: Uf1.9 (Zd), Uf2.8 (D3)
unnamed: Uf2.1 (~E), Uf5.3
unnamed: Uf4.3, Uf5.1
unnamed: Uf6.4 (Za), Uf7.3 (D0)
unnamed: Uf6.7 (Zb), Uf7.4 (D1)
unnamed: Uf6.12 (Zc), Uf7.7 (D2)
unnamed: Uf6.9 (Zd), Uf7.8 (D3)
unnamed: Uf5.6, Uf7.1 (~E)
unnamed: Uip1.9 (C4), Uip2.7 (C0)
unnamed: Uip2.9 (C4), Uip3.7 (C0)
unnamed: Uip3.9 (C4), Uip4.7 (C0)
unnamed: Uir1.4 (Za), Uir2.3 (D0)
unnamed: Uir1.7 (Zb), Uir2.4 (D1)
unnamed: Uir1.12 (Zc), Uir2.7 (D2)
unnamed: Uir1.9 (Zd), Uir2.8 (D3)
VCC: J1.1, J1.19, J2.1, J2.19, J3.1, J3.19, J4.1, J4.19, J5.1, J5.19, J6.1, J6.19, J7.1, J7.19, J8.9, J8.11, J8.13, J8.15, J8.17, J8.19, SW1.1, U4.4, U4.5, U4.14 (VCC), U57.9 (I0), U57.24 (VCC), Ubc1.16 (VCC), Ubc2.16 (VCC), Ubc3.5, Ubc3.9, Ubc3.13, Ubc3.14 (VCC), Ubd1.1 (A->B), Ubd1.20 (VCC), Ubd2.1 (A->B), Ubd2.20 (VCC), Ubd3.1 (A->B), Ubd3.20 (VCC), Ubd4.1 (A->B), Ubd4.20 (VCC), Ubd5.1 (A->B), Ubd5.20 (VCC), Ubd6.1 (A->B), Ubd6.20 (VCC), Ubd7.1 (A->B), Ubd7.20 (VCC), Ubd8.1 (A->B), Ubd8.20 (VCC), Ubd9.1 (A->B), Ubd9.20 (VCC), Ubd10.1 (A->B), Ubd10.20 (VCC), Ubd11.1 (A->B), Ubd11.20 (VCC), Ubd12.1 (A->B), Ubd12.20 (VCC), Ubd13.1 (A->B), Ubd13.20 (VCC), Ubd14.1 (A->B), Ubd14.20 (VCC), Ubd15.1 (A->B), Ubd15.20 (VCC), Ubd16.1 (A->B), Ubd16.20 (VCC), Ubd17.1 (A->B), Ubd17.20 (VCC), Ubd18.1 (A->B), Ubd18.20 (VCC), Ubd19.1 (A->B), Ubd19.20 (VCC), Ubd20.1 (A->B), Ubd20.20 (VCC), Ubu1.20 (VCC), Ubu2.20 (VCC), Ubu3.20 (VCC), Ubu4.20 (VCC), Ubu5.20 (VCC), Ubu6.20 (VCC), Ubu7.20 (VCC), Ubu8.20 (VCC), Ubu9.20 (VCC), Ubu10.20 (VCC), Ubu11.20 (VCC), Ubu12.20 (VCC), Ubu13.20 (VCC), Ubu14.20 (VCC), Ubu15.11 (B7), Ubu15.12 (B6), Ubu15.13 (B5), Ubu15.14 (B4), Ubu15.20 (VCC), Ubu16.11 (B7), Ubu16.12 (B6), Ubu16.13 (B5), Ubu16.14 (B4), Ubu16.15 (B3), Ubu16.16 (B2), Ubu16.17 (B1), Ubu16.18 (B0), Ubu16.20 (VCC), Ucr1.7 (C0), Ucr1.16 (VCC), Ucr2.16 (VCC), Ucr3.13 (D4), Ucr3.14 (D5), Ucr3.17 (D6), Ucr3.18 (D7), Ucr3.20 (VCC), Ud1.27 (~WE), Ud1.28 (VCC), Ud2.27 (~WE), Ud2.28 (VCC), Ud3.27 (~WE), Ud3.28 (VCC), Ud4.27 (~WE), Ud4.28 (VCC), Uf1.16 (VCC), Uf2.13 (D4), Uf2.14 (D5), Uf2.17 (D6), Uf2.18 (D7), Uf2.20 (VCC), Uf3.14 (VCC), Uf4.12, Uf4.13, Uf4.14 (VCC), Uf5.2, Uf5.5, Uf5.13, Uf5.14 (VCC), Uf6.16 (VCC), Uf7.13 (D4), Uf7.14 (D5), Uf7.17 (D6), Uf7.18 (D7), Uf7.20 (VCC), Uinsr1.16 (VCC), Uip1.6 (B1), Uip1.16 (VCC), Uip2.16 (VCC), Uip3.16 (VCC), Uip4.16 (VCC), Uip5.20 (V_{CC}), Uir1.16 (VCC), Uir2.13 (D4), Uir2.14 (D5), Uir2.17 (D6), Uir2.18 (D7), Uir2.20 (VCC), Ur1.20 (VCC), Ur2.20 (VCC), Ur3.20 (VCC), Ur4.20 (VCC), Ur5.20 (VCC), Ur6.20 (VCC)

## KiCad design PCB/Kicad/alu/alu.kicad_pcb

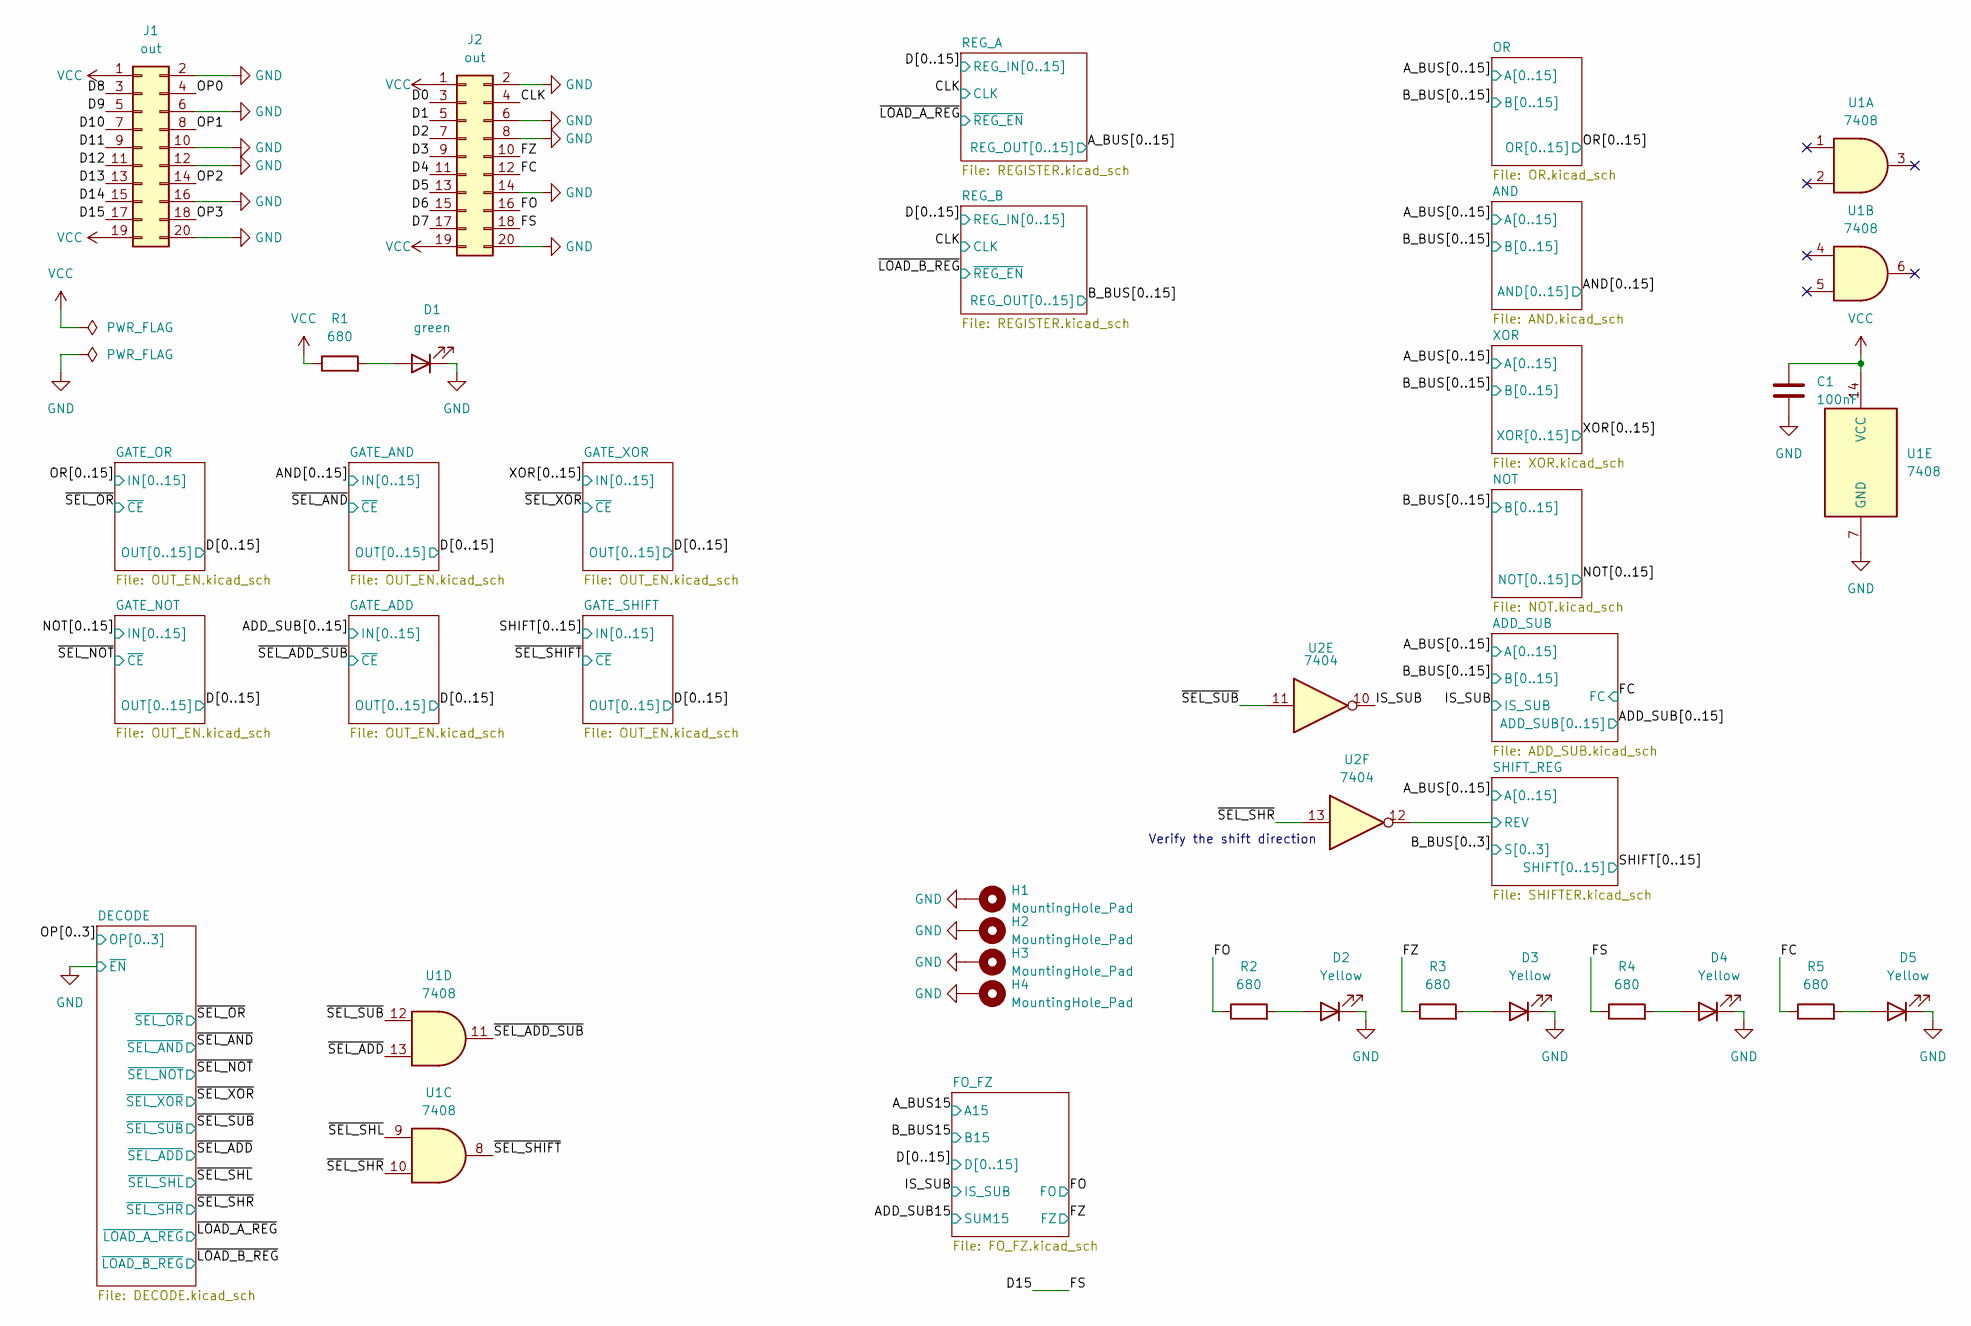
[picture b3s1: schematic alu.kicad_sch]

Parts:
C1: 100nF; C_0402_1005Metric
D1: green; LED_0603_1608Metric
D2, D3, D4, D5: Yellow; LED_0603_1608Metric
H1, H2, H3, H4: MountingHole_Pad; MountingHole_2.2mm_M2_DIN965_Pad
J1, J2: out; PinHeader_2x10_P2.54mm_Horizontal
R1, R2, R3, R4, R5: 680; R_0402_1005Metric
U1: 7408; SO-14_3.9x8.65mm_P1.27mm
U2: 7404; SO-14_3.9x8.65mm_P1.27mm

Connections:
/CLK: J2.4; also elsewhere on the board
/D0: J2.3; also elsewhere on the board
/D1: J2.5; also elsewhere on the board
/D2: J2.7; also elsewhere on the board
/D3: J2.9; also elsewhere on the board
/D4: J2.11; also elsewhere on the board
/D5: J2.13; also elsewhere on the board
/D6: J2.15; also elsewhere on the board
/D7: J2.17; also elsewhere on the board
/D8: J1.3; also elsewhere on the board
/D9: J1.5; also elsewhere on the board
/D10: J1.7; also elsewhere on the board
/D11: J1.9; also elsewhere on the board
/D12: J1.11; also elsewhere on the board
/D13: J1.13; also elsewhere on the board
/D14: J1.15; also elsewhere on the board
/D15: J1.17, J2.18, R4.1; also elsewhere on the board
/FC: J2.12, R5.1; also elsewhere on the board
/FO: J2.16, R2.1; also elsewhere on the board
/FZ: J2.10, R3.1; also elsewhere on the board
/IS_SUB: U2.10; also elsewhere on the board
/OP0: J1.4; also elsewhere on the board
/OP1: J1.8; also elsewhere on the board
/OP2: J1.14; also elsewhere on the board
/OP3: J1.18; also elsewhere on the board
/SHIFT_REG/REV: U2.12; also elsewhere on the board
/~SEL_ADD_SUB: U1.11; also elsewhere on the board
/~SEL_ADD: U1.13; also elsewhere on the board
/~SEL_SHIFT: U1.8; also elsewhere on the board
/~SEL_SHL: U1.9; also elsewhere on the board
/~SEL_SHR: U1.10, U2.13; also elsewhere on the board
/~SEL_SUB: U1.12, U2.11; also elsewhere on the board
GND: C1.2, D1.1 (K), D2.1 (K), D3.1 (K), D4.1 (K), D5.1 (K), H1.1 (1_1), H2.1 (1_1), H3.1 (1_1), H4.1 (1_1), J1.2, J1.6, J1.10, J1.12, J1.16, J1.20, J2.2, J2.6, J2.8, J2.14, J2.20, U1.7 (GND); also elsewhere on the board
unnamed: D1.2 (A), R1.2
unnamed: D2.2 (A), R2.2
unnamed: D3.2 (A), R3.2
unnamed: D4.2 (A), R4.2
unnamed: D5.2 (A), R5.2
VCC: C1.1, J1.1, J1.19, J2.1, J2.19, R1.1, U1.14 (VCC); also elsewhere on the board

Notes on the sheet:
Verify the shift direction
